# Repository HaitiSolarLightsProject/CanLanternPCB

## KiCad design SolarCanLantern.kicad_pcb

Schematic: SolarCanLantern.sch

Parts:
BT1: Battery_Cell; Socket_Strip_Straight_1x02_Pitch2.00mm
C1: 0.1µF; C_0805_HandSoldering
C2: 10µF; C_0805_HandSoldering
D1, D2: LED; LED_0805_HandSoldering
Q1, Q2: 2N7002; SOT-23
R1: 287K; R_0805_HandSoldering
R2: 88.7K; R_0805_HandSoldering
R3, R4: 10Ω; R_0805_HandSoldering
SC1: Solar_Cell; Socket_Strip_Straight_1x02_Pitch2.00mm
SW1: SW_Push; SW_Tactile_SKHH_Angled
U1: ATTINY13-20SSU; SOIC-8_3.9x4.9mm_Pitch1.27mm
U2: MAX40200; TSOT-23-5_HandSoldering

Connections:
+BATT: BT1.1, C2.1, R1.1, R3.1, R4.1, U1.8 (VCC), U2.5
/LEDA: Q1.1 (G), U1.5 (PB0(MOSI/AIN0/OC0A/PCINT0))
/LEDB: Q2.1 (G), U1.6 (PB1(MISO/AIN1/OC0B/INT0/PCINT1))
/SolarIn: SC1.1, U2.1
/Switch: SW1.2, U1.3 (PB4(ADC2/PCINT4))
/VBatt_Divider: C1.1, R1.2, R2.1, U1.7 (PB2(SCK/ADC1/T0/PCINT2))
/~SOLAR: U1.2 (PB3(CLKI/ADC3/PCINT3)), U2.3
GND: BT1.2, C1.2, C2.2, Q1.2 (S), Q2.2 (S), R2.2, SC1.2, SW1.1, U1.4 (GND), U2.2
unnamed: D1.1, Q1.3 (D)
unnamed: D1.2, R3.2
unnamed: D2.1, Q2.3 (D)
unnamed: D2.2, R4.2

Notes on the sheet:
Note: There are only 2 PWM capable pins so LEDS A and B are on PWM capable pins, while C is not

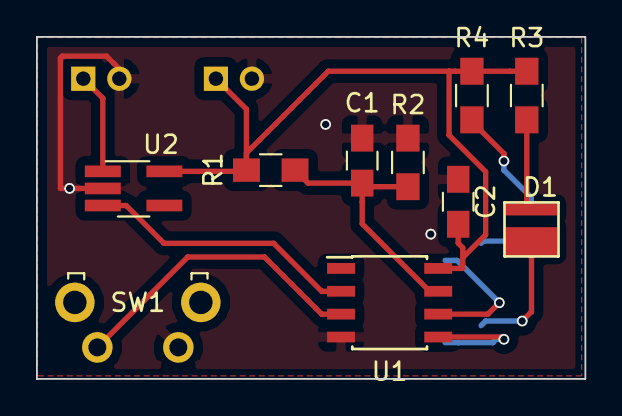
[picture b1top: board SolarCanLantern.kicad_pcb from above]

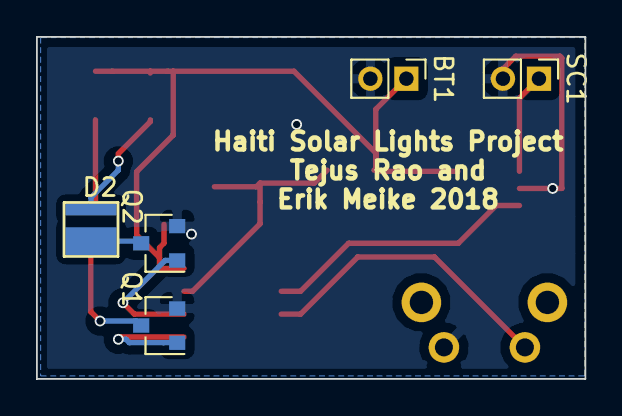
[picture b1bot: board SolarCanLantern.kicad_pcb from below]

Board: 2 copper layers, 30.5 x 19.0 mm, 15 parts (5 on the bottom side), 12 nets.

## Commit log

2018-04-03 resolved some library problems and switched to mosfets as a test
2018-04-03 fixed accidental swap of solar enable and adc
2018-04-08 remove netlist
2018-04-08 add footprints
2018-04-08 start of layout
2018-04-22 first rev pcb layout with no button
2018-05-04 Added switch and completed first PCB layout
2018-10-06 got latest version from tejus and modified
2018-10-06 exported gerbers
2018-10-18 slightly reorganize board
2018-10-18 added missing library
2018-10-18 added more missing footprints
2018-10-18 add sym-lib-table
